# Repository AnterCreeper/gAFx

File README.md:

- core: main process board, including controller, FPGA, Audio DAC, EEPROM, battery charger and potentiometers(with buttons)
- pickguard: CAD file of pickguard
- pickup: Analog FrontEnd of pickup and Reflective Screen, sample signal from pickup and transport to main board via PDM signal in stereo
- plug: Plugs, including Type-C(may support Type-C Analog Headphone), SDcard, Headphone Out Jack, Line In Jack, Switch(mux between Bluetooth Receiver and Analog Line In)

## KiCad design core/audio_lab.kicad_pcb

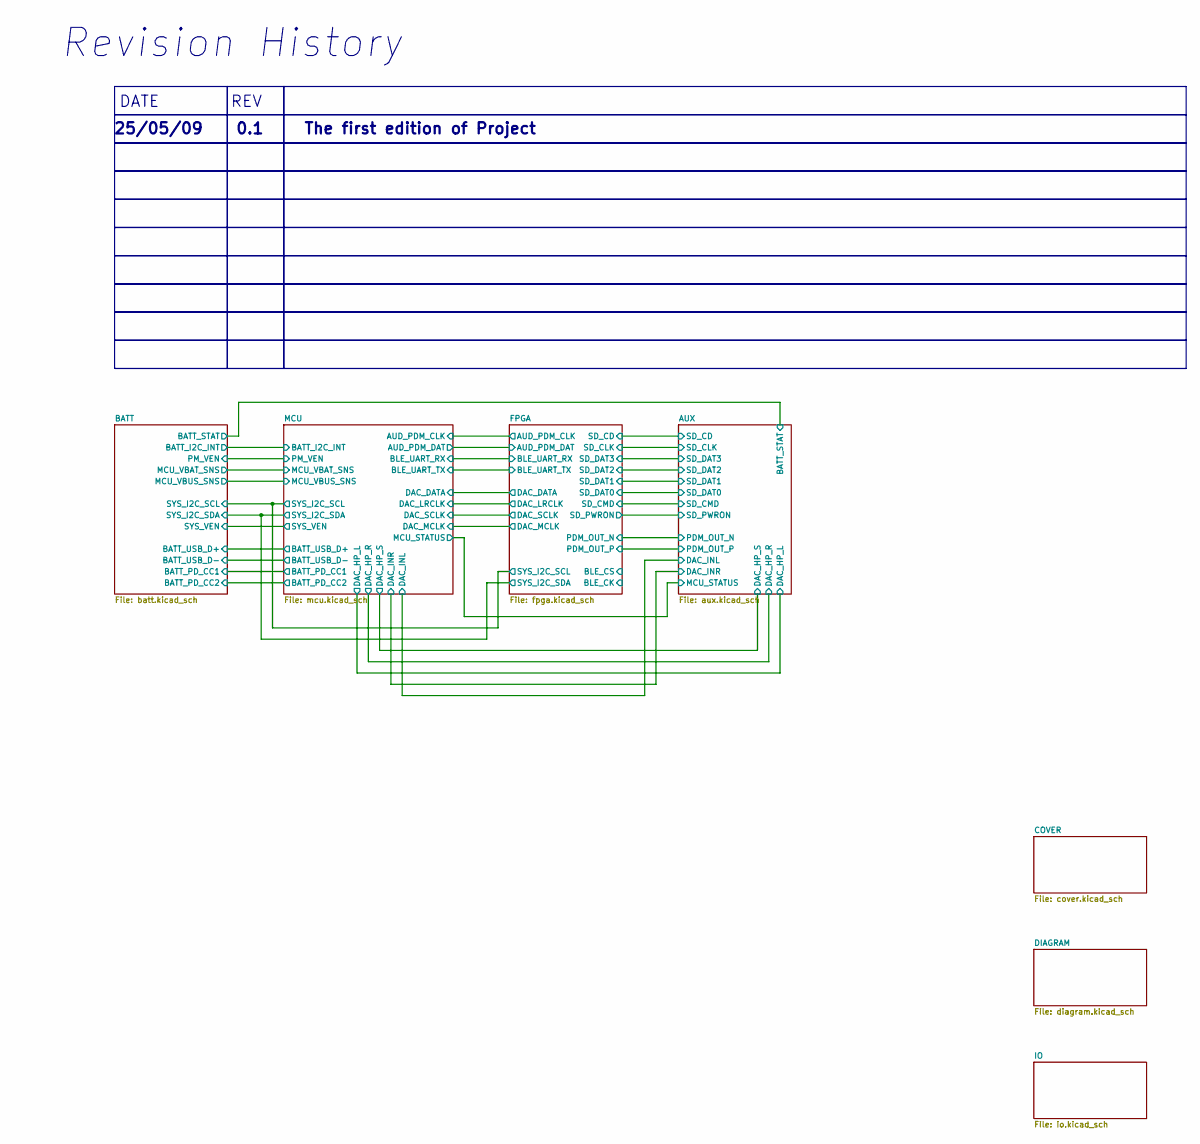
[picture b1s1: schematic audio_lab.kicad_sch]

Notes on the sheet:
Revision History
REV
0.1
25/05/09
The first edition of Project
DATE

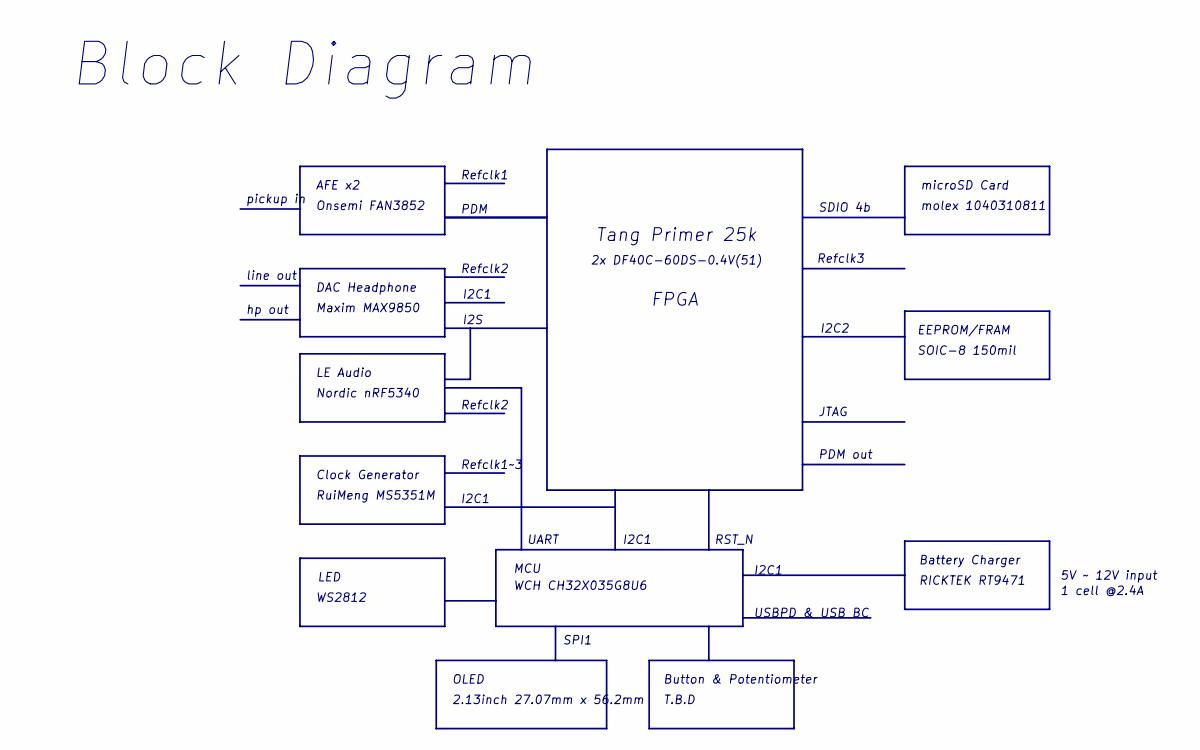
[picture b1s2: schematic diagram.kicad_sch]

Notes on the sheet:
T.B.D
Onsemi FAN3852
Clock Generator
line out
FPGA
PDM out
WCH CH32X035G8U6
5V ~ 12V input
Refclk2
RuiMeng MS5351M
USBPD & USB BC
Refclk3
JTAG
EEPROM/FRAM
Refclk1
I2C1
hp out
WS2812
microSD Card
SOIC-8 150mil
Maxim MAX9850
OLED
RICKTEK RT9471
molex 1040310811
Nordic nRF5340
LE Audio
PDM
Button & Potentiometer
Block Diagram
LED
pickup in
UART
DAC Headphone
I2C2
SDIO 4b
2.13inch 27.07mm x 56.2mm
AFE x2
SPI1
2x DF40C-60DS-0.4V(51)
MCU

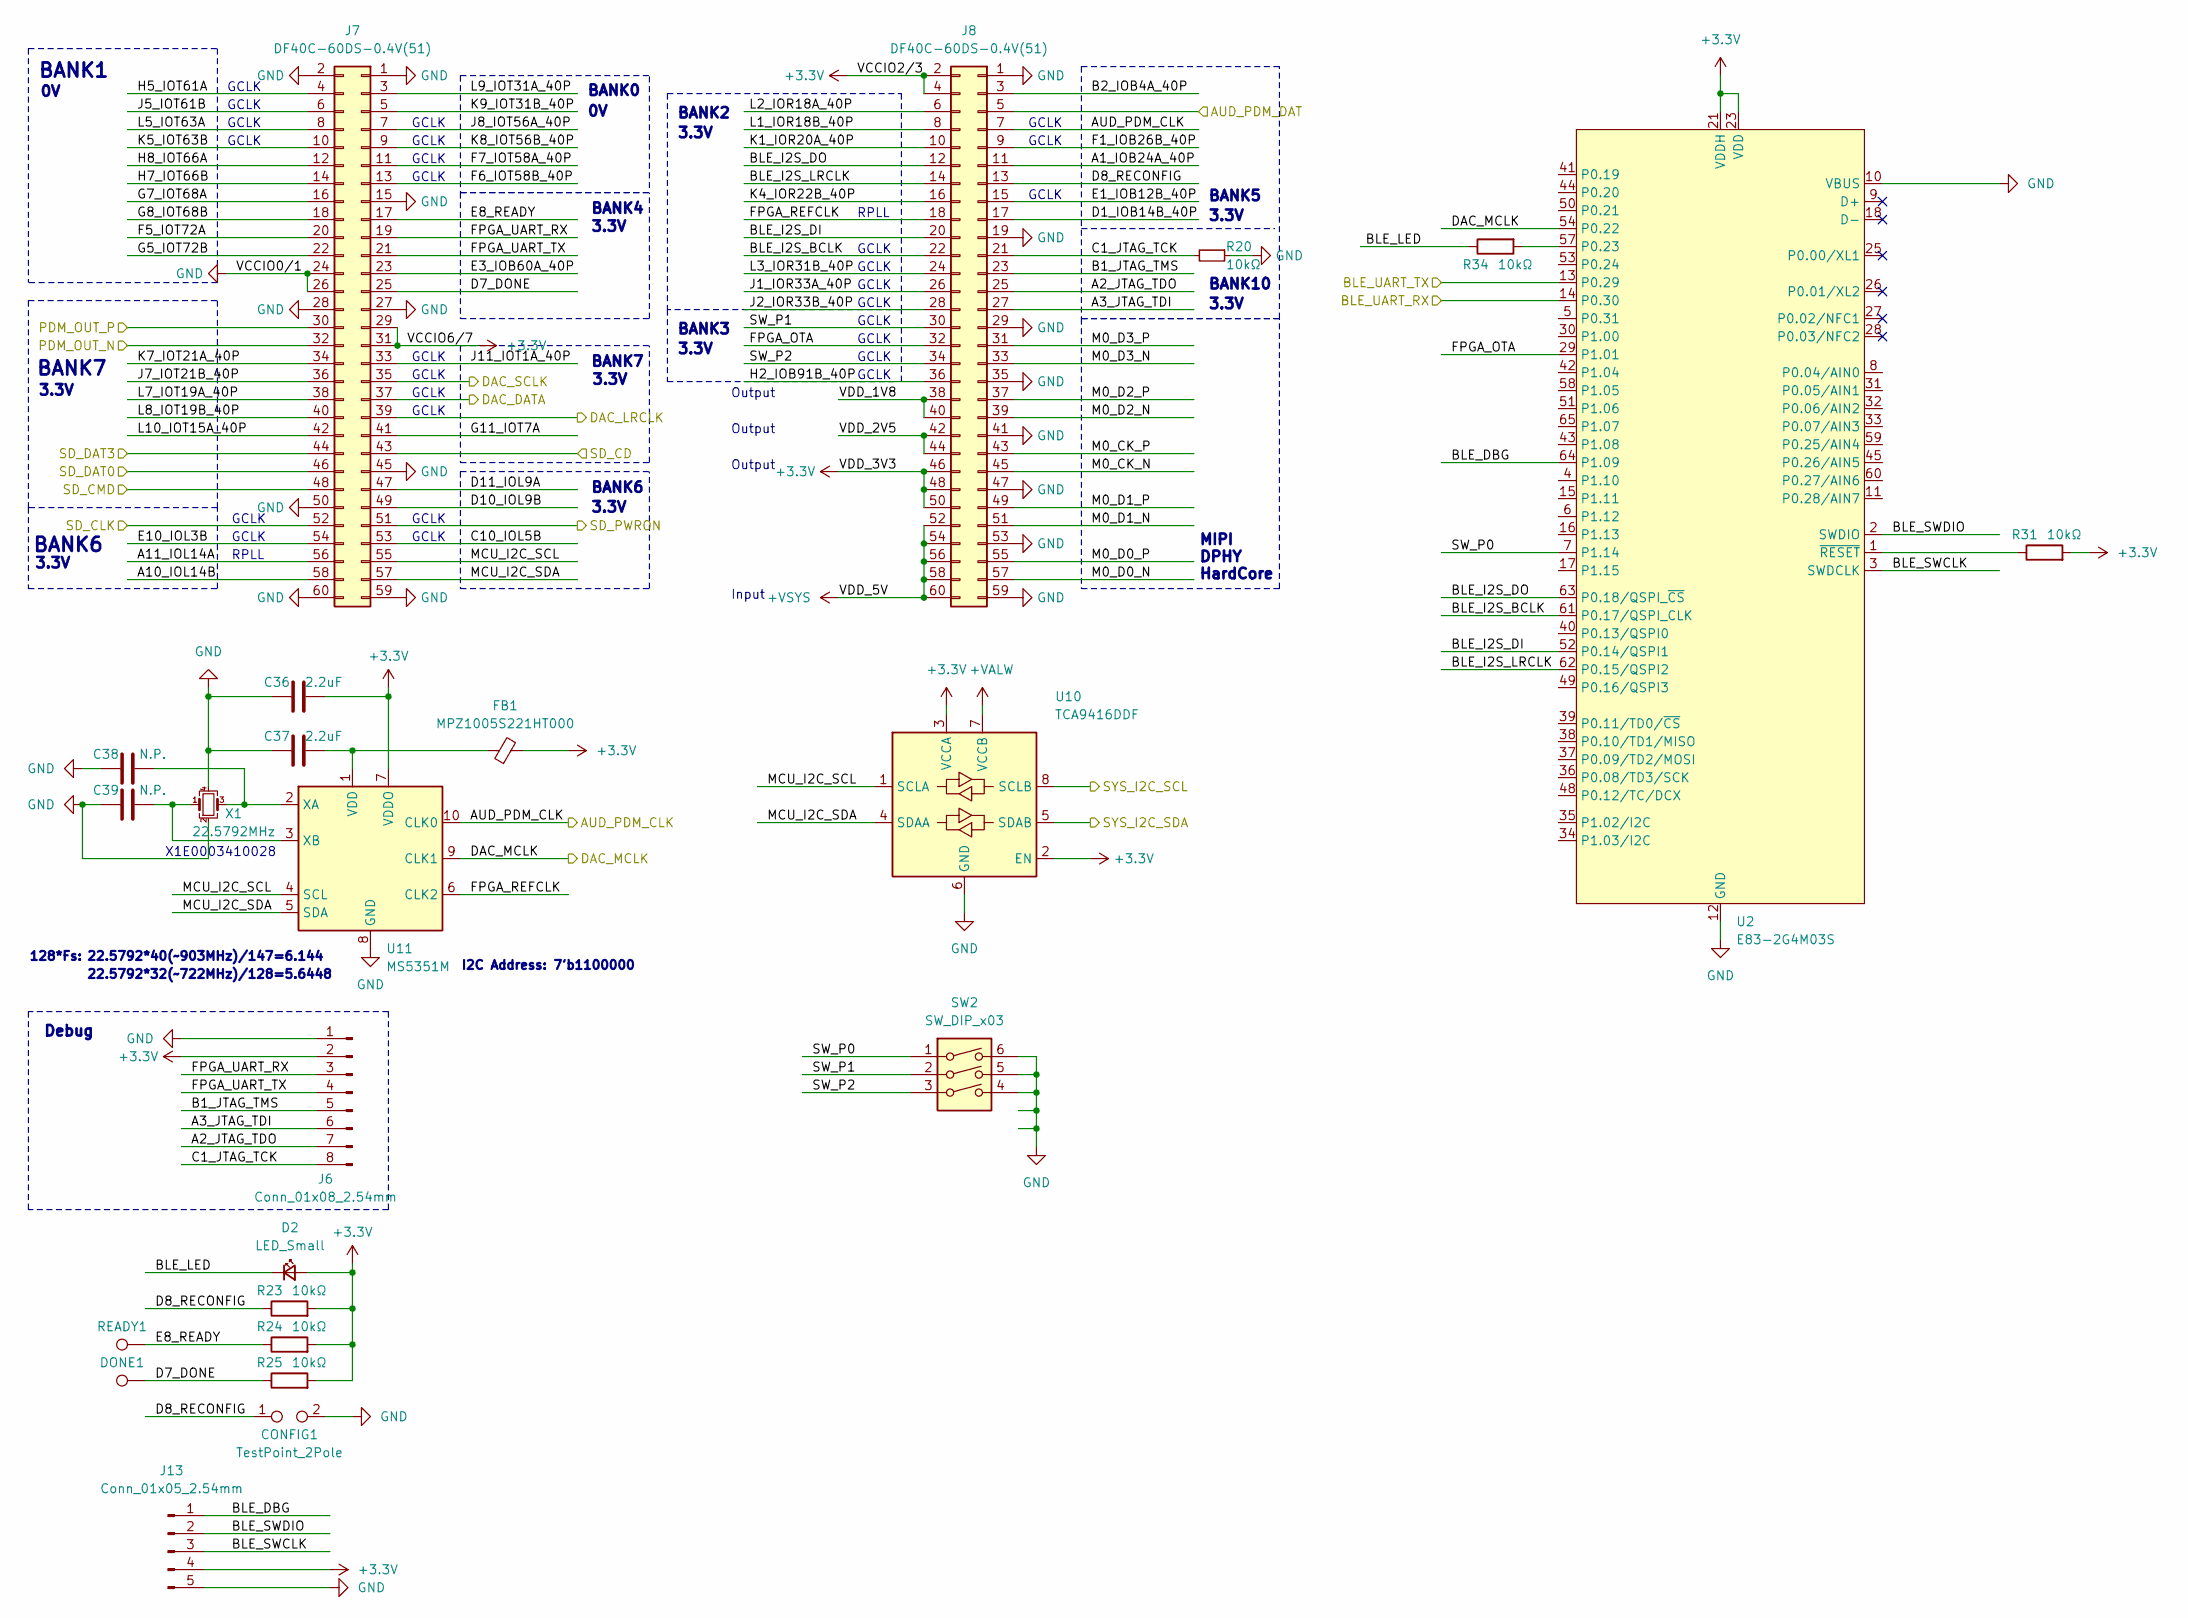
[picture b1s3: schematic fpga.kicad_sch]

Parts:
C36, C37: 2.2uF; C_0402_1005Metric
C38, C39: N.P.; C_0402_1005Metric
CONFIG1: TestPoint_2Pole; TestPoint_Bridge_Pitch2.0mm_Drill0.7mm
D2: LED_Small; D_0603_1608Metric
DONE1: TestPoint; TestPoint_Pad_D1.0mm
FB1: MPZ1005S221HT000; L_0402_1005Metric
J6: Conn_01x08_2.54mm; PinHeader_1x08_P2.54mm_Vertical
J7, J8: DF40C-60DS-0.4V(51); BTB-DF40C-60DS-0.4V(51)
J13: Conn_01x05_2.54mm; PinHeader_1x05_P2.54mm_Vertical
R20, R23, R24, R25, R31, R34: 10kΩ; R_0402_1005Metric
READY1: TestPoint; TestPoint_Pad_D1.0mm
SW2: SW_DIP_x03; SW_DIP_SPSTx03_Slide_KingTek_DSHP03TS_W7.62mm_P1.27mm
U2: E83-2G4M03S; E83-2G4M03S_16x16mm_LGA; LCSC C5333991
U10: TCA9416DDF; TSOT-23-8
U11: MS5351M; MSOP-10_3x3mm_P0.5mm
X1: 22.5792MHz; Crystal_SMD_3225-4Pin_3.2x2.5mm

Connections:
+3.3V: C36.2, D2.2 (A), FB1.2, J6.2, J7.29, J7.31, J8.2, J8.4, J8.46, J8.48, J8.50, J13.4, R23.2, R24.2, R25.2, R31.2, U2.21 (VDDH), U2.23 (VDD), U10.2 (EN), U10.3 (VCCA), U11.7 (VDDO); also elsewhere on the board
+VALW: U10.7 (VCCB); also elsewhere on the board
+VSYS: J8.52, J8.54, J8.56, J8.58, J8.60; also elsewhere on the board
/AUX/PDM_OUT_N: J7.32; also elsewhere on the board
/AUX/PDM_OUT_P: J7.30; also elsewhere on the board
/AUX/SD_CD: J7.43; also elsewhere on the board
/AUX/SD_CLK: J7.52; also elsewhere on the board
/AUX/SD_CMD: J7.48; also elsewhere on the board
/AUX/SD_DAT0: J7.46; also elsewhere on the board
/AUX/SD_DAT3: J7.44; also elsewhere on the board
/AUX/SD_PWRON: J7.51; also elsewhere on the board
/FPGA/A1_IOB24A_40P: J8.11
/FPGA/A2_JTAG_TDO: J6.7, J8.25
/FPGA/A3_JTAG_TDI: J6.6, J8.27
/FPGA/A10_IOL14B: J7.58
/FPGA/A11_IOL14A: J7.56
/FPGA/AUD_PDM_CLK: J8.7, U11.10 (CLK0); also elsewhere on the board
/FPGA/AUD_PDM_DAT: J8.5; also elsewhere on the board
/FPGA/B1_JTAG_TMS: J6.5, J8.23
/FPGA/B2_IOB4A_40P: J8.3
/FPGA/BLE_DBG: J13.1, U2.64 (P1.09)
/FPGA/BLE_I2S_BCLK: J8.22, U2.61 (P0.17/QSPI_CLK)
/FPGA/BLE_I2S_DI: J8.20, U2.52 (P0.14/QSPI1)
/FPGA/BLE_I2S_DO: J8.12, U2.63 (P0.18/QSPI_~CS)
/FPGA/BLE_I2S_LRCLK: J8.14, U2.62 (P0.15/QSPI2)
/FPGA/BLE_LED: D2.1 (K), R34.1
/FPGA/BLE_SWCLK: J13.3, U2.3 (SWDCLK)
/FPGA/BLE_SWDIO: J13.2, U2.2 (SWDIO)
/FPGA/BLE_UART_RX: U2.14 (P0.30); also elsewhere on the board
/FPGA/BLE_UART_TX: U2.13 (P0.29); also elsewhere on the board
/FPGA/C1_JTAG_TCK: J6.8, J8.21, R20.2
/FPGA/C10_IOL5B: J7.53
/FPGA/D1_IOB14B_40P: J8.17
/FPGA/D7_DONE: DONE1.1, J7.25, R25.1; also elsewhere on the board
/FPGA/D8_RECONFIG: CONFIG1.1, J8.13, R23.1; also elsewhere on the board
/FPGA/D10_IOL9B: J7.49
/FPGA/D11_IOL9A: J7.47
/FPGA/DAC_DATA: J7.37; also elsewhere on the board
/FPGA/DAC_LRCLK: J7.39; also elsewhere on the board
/FPGA/DAC_MCLK: U2.54 (P0.22), U11.9 (CLK1); also elsewhere on the board
/FPGA/DAC_SCLK: J7.35; also elsewhere on the board
/FPGA/E1_IOB12B_40P: J8.15
/FPGA/E3_IOB60A_40P: J7.23
/FPGA/E8_READY: J7.17, R24.1, READY1.1; also elsewhere on the board
/FPGA/E10_IOL3B: J7.54
/FPGA/F1_IOB26B_40P: J8.9
/FPGA/F5_IOT72A: J7.20
/FPGA/F6_IOT58B_40P: J7.13
/FPGA/F7_IOT58A_40P: J7.11
/FPGA/FPGA_OTA: J8.32, U2.29 (P1.01)
/FPGA/FPGA_REFCLK: J8.18, U11.6 (CLK2)
/FPGA/FPGA_UART_RX: J6.3, J7.19
/FPGA/FPGA_UART_TX: J6.4, J7.21
/FPGA/G5_IOT72B: J7.22
/FPGA/G7_IOT68A: J7.16
/FPGA/G8_IOT68B: J7.18
/FPGA/G11_IOT7A: J7.41
/FPGA/H2_IOB91B_40P: J8.36
/FPGA/H5_IOT61A: J7.4
/FPGA/H7_IOT66B: J7.14
/FPGA/H8_IOT66A: J7.12
/FPGA/J1_IOR33A_40P: J8.26
/FPGA/J2_IOR33B_40P: J8.28
/FPGA/J5_IOT61B: J7.6
/FPGA/J7_IOT21B_40P: J7.36
/FPGA/J8_IOT56A_40P: J7.7
/FPGA/J11_IOT1A_40P: J7.33
/FPGA/K1_IOR20A_40P: J8.10
/FPGA/K4_IOR22B_40P: J8.16
/FPGA/K5_IOT63B: J7.10
/FPGA/K7_IOT21A_40P: J7.34
/FPGA/K8_IOT56B_40P: J7.9
/FPGA/K9_IOT31B_40P: J7.5
/FPGA/L1_IOR18B_40P: J8.8
/FPGA/L2_IOR18A_40P: J8.6
/FPGA/L3_IOR31B_40P: J8.24
/FPGA/L5_IOT63A: J7.8
/FPGA/L7_IOT19A_40P: J7.38
/FPGA/L8_IOT19B_40P: J7.40
/FPGA/L9_IOT31A_40P: J7.3
/FPGA/L10_IOT15A_40P: J7.42
/FPGA/M0_CK_N: J8.45
/FPGA/M0_CK_P: J8.43
/FPGA/M0_D0_N: J8.57
/FPGA/M0_D0_P: J8.55
/FPGA/M0_D1_N: J8.51
/FPGA/M0_D1_P: J8.49
/FPGA/M0_D2_N: J8.39
/FPGA/M0_D2_P: J8.37
/FPGA/M0_D3_N: J8.33
/FPGA/M0_D3_P: J8.31
/FPGA/MCU_I2C_SCL: J7.55, U10.1 (SCLA), U11.4 (SCL)
/FPGA/MCU_I2C_SDA: J7.57, U10.4 (SDAA), U11.5 (SDA)
/FPGA/SW_P0: SW2.1, U2.7 (P1.14)
/FPGA/SW_P1: J8.30, SW2.2
/FPGA/SW_P2: J8.34, SW2.3
/FPGA/VDD_1V8: J8.38, J8.40
/FPGA/VDD_2V5: J8.42, J8.44
/MCU/MCU_I2C_SCL: U10.8 (SCLB); also elsewhere on the board
/MCU/MCU_I2C_SDA: U10.5 (SDAB); also elsewhere on the board
GND: C36.1, C37.1, C38.1, C39.1, CONFIG1.2, J6.1, J7.1, J7.2, J7.15, J7.24, J7.26, J7.27, J7.28, J7.45, J7.50, J7.59, J7.60, J8.1, J8.19, J8.29, J8.35, J8.41, J8.47, J8.53, J8.59, J13.5, R20.1, SW2.4, SW2.5, SW2.6, U2.10 (VBUS), U2.12 (GND), U2.19 (GND), U2.20 (GND), U2.22 (GND), U2.24 (GND), U2.46 (GND), U2.47 (GND), U2.55 (GND), U2.56 (GND), U10.6 (GND), U11.8 (GND), X1.2, X1.4; also elsewhere on the board
unnamed: R34.2, U2.57 (P0.23)
unnamed: R31.1, U2.1 (~RESET)
unnamed: C37.2, FB1.1, U11.1 (VDD)
unnamed: C38.2, U11.2 (XA), X1.3
unnamed: C39.2, U11.3 (XB), X1.1

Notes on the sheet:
GCLK
BANK6
RPLL
BANK2
22.5792*32(~722MHz)/128=5.6448
Debug
3.3V
BANK10
MIPI DPHY HardCore
BANK4
BANK5
X1E0003410028
Input
Output
BANK7
I2C Address: 7'b1100000
128*Fs:
BANK1
22.5792*40(~903MHz)/147=6.144
BANK3
BANK0

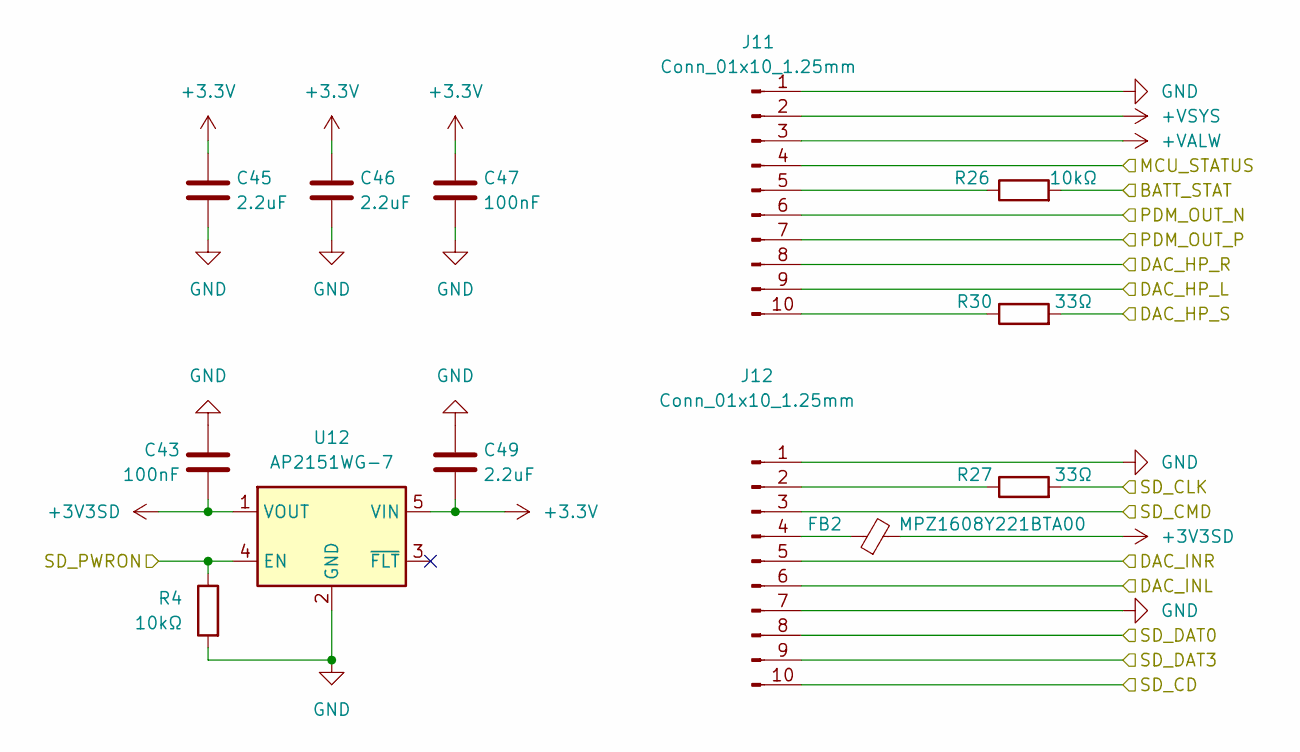
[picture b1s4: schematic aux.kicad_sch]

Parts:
C43, C47: 100nF; C_0402_1005Metric
C45, C46, C49: 2.2uF; C_0402_1005Metric
FB2: MPZ1608Y221BTA00; L_0603_1608Metric
J11, J12: Conn_01x10_1.25mm; Molex_PicoBlade_53047-1010_1x10_P1.25mm_Vertical
R4, R26: 10kΩ; R_0402_1005Metric
R27, R30: 33Ω; R_0402_1005Metric
U12: AP2151WG-7; SOT-23-5

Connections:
+3.3V: C45.1, C46.1, C47.1, C49.2, U12.5 (VIN); also elsewhere on the board
+3V3SD: C43.2, FB2.2, U12.1 (VOUT)
+VALW: J11.3; also elsewhere on the board
+VSYS: J11.2; also elsewhere on the board
/AUX/BATT_STAT: R26.2; also elsewhere on the board
/AUX/DAC_HP_L: J11.9; also elsewhere on the board
/AUX/DAC_HP_R: J11.8; also elsewhere on the board
/AUX/DAC_HP_S: R30.2; also elsewhere on the board
/AUX/DAC_INL: J12.6; also elsewhere on the board
/AUX/DAC_INR: J12.5; also elsewhere on the board
/AUX/MCU_STATUS: J11.4; also elsewhere on the board
/AUX/PDM_OUT_N: J11.6; also elsewhere on the board
/AUX/PDM_OUT_P: J11.7; also elsewhere on the board
/AUX/SD_CD: J12.10; also elsewhere on the board
/AUX/SD_CLK: R27.2; also elsewhere on the board
/AUX/SD_CMD: J12.3; also elsewhere on the board
/AUX/SD_DAT0: J12.8; also elsewhere on the board
/AUX/SD_DAT3: J12.9; also elsewhere on the board
/AUX/SD_PWRON: R4.1, U12.4 (EN); also elsewhere on the board
GND: C43.1, C45.2, C46.2, C47.2, C49.1, J11.1, J12.1, J12.7, R4.2, U12.2 (GND); also elsewhere on the board
unnamed: J11.5, R26.1
unnamed: J11.10, R30.1
unnamed: J12.2, R27.1
unnamed: FB2.1, J12.4

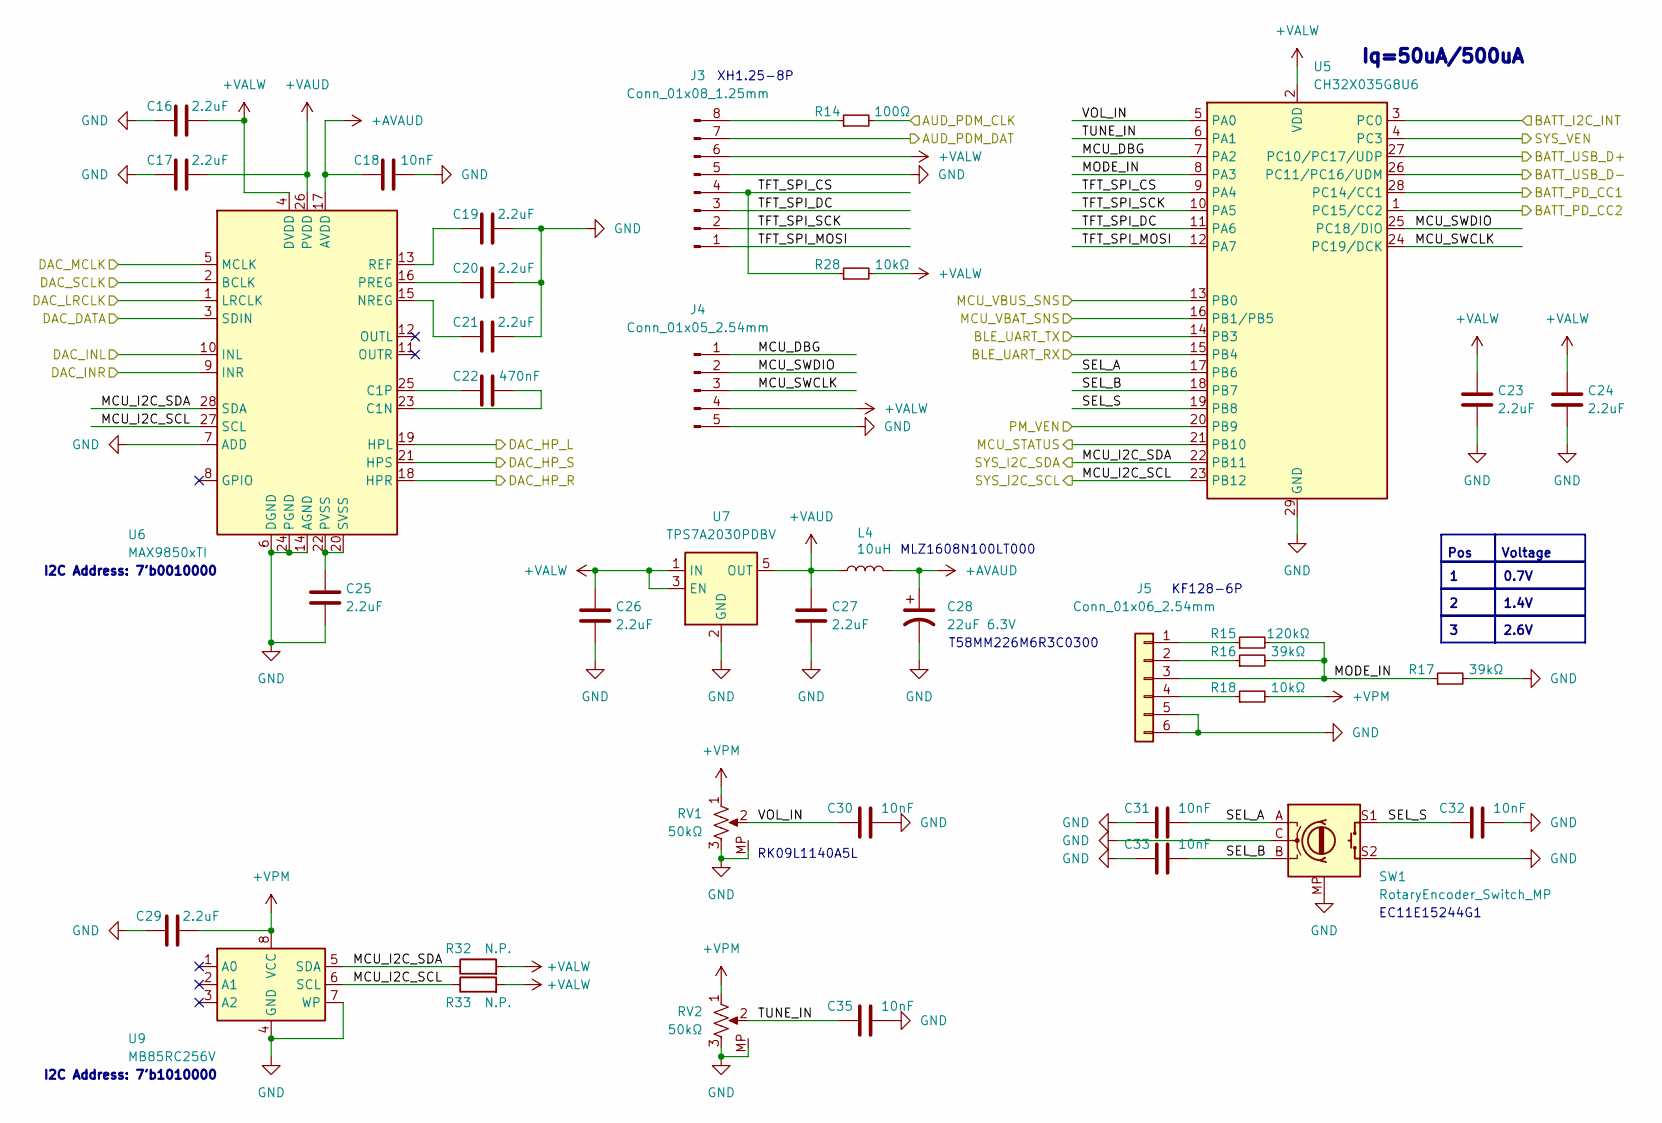
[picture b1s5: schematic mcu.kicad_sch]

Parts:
C16, C17, C19, C20, C21, C23, C24, C25, C26, C27, C29: 2.2uF; C_0402_1005Metric
C18, C30, C31, C32, C33, C35: 10nF; C_0402_1005Metric
C22: 470nF; C_0402_1005Metric
C28: 22uF 6.3V; CP_EIA-1608-08_AVX-J
J3: Conn_01x08_1.25mm; Molex_PicoBlade_53047-0810_1x08_P1.25mm_Vertical
J4: Conn_01x05_2.54mm; PinHeader_1x05_P2.54mm_Vertical
J5: Conn_01x06_2.54mm; PinSocket_1x06_P2.54mm_Vertical
L4: 10uH; L_0603_1608Metric
R14: 100Ω; R_0402_1005Metric
R15: 120kΩ; R_0402_1005Metric
R16, R17: 39kΩ; R_0402_1005Metric
R18, R28: 10kΩ; R_0402_1005Metric
R32, R33: N.P.; R_0402_1005Metric
RV1, RV2: 50kΩ; Potentiometer_Alpha_RD901F-40-00D_Single_Vertical
SW1: RotaryEncoder_Switch_MP; RotaryEncoder_Favor_FEC11_Vertical_H15mm
U5: CH32X035G8U6; QFN-28-1EP_4x4mm_P0.4mm_EP2.7x2.7mm
U6: MAX9850xTI; TQFN-28-1EP_5x5mm_P0.5mm_EP3.25x3.25mm_ThermalVias
U7: TPS7A2030PDBV; SOT-23-5
U9: MB85RC256V; SOIC-8_3.9x4.9mm_P1.27mm

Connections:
+AVAUD: C18.1, C28.1, L4.2, U6.17 (AVDD)
+VALW: C16.2, C23.1, C24.1, C26.1, J3.6, J4.4, R28.2, R32.2, R33.2, U5.2 (VDD), U6.4 (DVDD), U7.1 (IN), U7.3 (EN); also elsewhere on the board
+VAUD: C17.2, C27.1, L4.1, U6.26 (PVDD), U7.5 (OUT)
+VPM: C29.2, R18.2, RV1.1, RV2.1, U9.8 (VCC); also elsewhere on the board
/AUX/DAC_HP_L: U6.19 (HPL); also elsewhere on the board
/AUX/DAC_HP_R: U6.18 (HPR); also elsewhere on the board
/AUX/DAC_HP_S: U6.21 (HPS); also elsewhere on the board
/AUX/DAC_INL: U6.10 (INL); also elsewhere on the board
/AUX/DAC_INR: U6.9 (INR); also elsewhere on the board
/AUX/MCU_STATUS: U5.21 (PB10); also elsewhere on the board
/BATT/BATT_I2C_INT: U5.3 (PC0); also elsewhere on the board
/BATT/BATT_PD_CC1: U5.28 (PC14/CC1); also elsewhere on the board
/BATT/BATT_PD_CC2: U5.1 (PC15/CC2); also elsewhere on the board
/BATT/BATT_USB_D+: U5.27 (PC10/PC17/UDP); also elsewhere on the board
/BATT/BATT_USB_D-: U5.26 (PC11/PC16/UDM); also elsewhere on the board
/BATT/MCU_VBAT_SNS: U5.16 (PB1/PB5); also elsewhere on the board
/BATT/MCU_VBUS_SNS: U5.13 (PB0); also elsewhere on the board
/BATT/PM_VEN: U5.20 (PB9); also elsewhere on the board
/BATT/SYS_VEN: U5.4 (PC3); also elsewhere on the board
/FPGA/AUD_PDM_CLK: R14.2; also elsewhere on the board
/FPGA/AUD_PDM_DAT: J3.7; also elsewhere on the board
/FPGA/BLE_UART_RX: U5.15 (PB4); also elsewhere on the board
/FPGA/BLE_UART_TX: U5.14 (PB3); also elsewhere on the board
/FPGA/DAC_DATA: U6.3 (SDIN); also elsewhere on the board
/FPGA/DAC_LRCLK: U6.1 (LRCLK); also elsewhere on the board
/FPGA/DAC_MCLK: U6.5 (MCLK); also elsewhere on the board
/FPGA/DAC_SCLK: U6.2 (BCLK); also elsewhere on the board
/MCU/MCU_DBG: J4.1, U5.7 (PA2)
/MCU/MCU_I2C_SCL: R33.1, U5.23 (PB12), U6.27 (SCL), U9.6 (SCL); also elsewhere on the board
/MCU/MCU_I2C_SDA: R32.1, U5.22 (PB11), U6.28 (SDA), U9.5 (SDA); also elsewhere on the board
/MCU/MCU_SWCLK: J4.3, U5.24 (PC19/DCK)
/MCU/MCU_SWDIO: J4.2, U5.25 (PC18/DIO)
/MCU/MODE_IN: J5.3, R15.2, R16.2, R17.1, U5.8 (PA3)
/MCU/SEL_A: C31.2, SW1.A, U5.17 (PB6)
/MCU/SEL_B: C33.2, SW1.B, U5.18 (PB7)
/MCU/SEL_S: C32.1, SW1.S1, U5.19 (PB8)
/MCU/TFT_SPI_CS: J3.4, R28.1, U5.9 (PA4)
/MCU/TFT_SPI_DC: J3.3, U5.11 (PA6)
/MCU/TFT_SPI_MOSI: J3.1, U5.12 (PA7)
/MCU/TFT_SPI_SCK: J3.2, U5.10 (PA5)
/MCU/TUNE_IN: C35.1, RV2.2, U5.6 (PA1)
/MCU/VOL_IN: C30.1, RV1.2, U5.5 (PA0)
GND: C16.1, C17.1, C18.2, C19.2, C20.2, C21.2, C23.2, C24.2, C25.2, C26.2, C27.2, C28.2, C29.1, C30.2, C31.1, C32.2, C33.1, C35.2, J3.5, J4.5, J5.5, J5.6, R17.2, RV1.3, RV1.MP, RV2.3, RV2.MP, SW1.C, SW1.MP, SW1.S2, U5.29 (GND), U6.6 (DGND), U6.7 (ADD), U6.14 (AGND), U6.24 (PGND), U6.29 (AGND), U7.2 (GND), U9.4 (GND), U9.7 (WP); also elsewhere on the board
unnamed: J3.8, R14.1
unnamed: J5.1, R15.1
unnamed: J5.2, R16.1
unnamed: J5.4, R18.1
unnamed: C22.2, U6.23 (C1N)
unnamed: C22.1, U6.25 (C1P)
unnamed: C21.1, U6.15 (NREG)
unnamed: C20.1, U6.16 (PREG)
unnamed: C25.1, U6.20 (SVSS), U6.22 (PVSS)
unnamed: C19.1, U6.13 (REF)

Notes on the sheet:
T58MM226M6R3C0300
Pos
Iq=50uA/500uA
RK09L1140A5L
MLZ1608N100LT000
0.7V
1.4V
XH1.25-8P
2.6V
I2C Address: 7'b1010000
Voltage
I2C Address: 7'b0010000
KF128-6P
EC11E15244G1

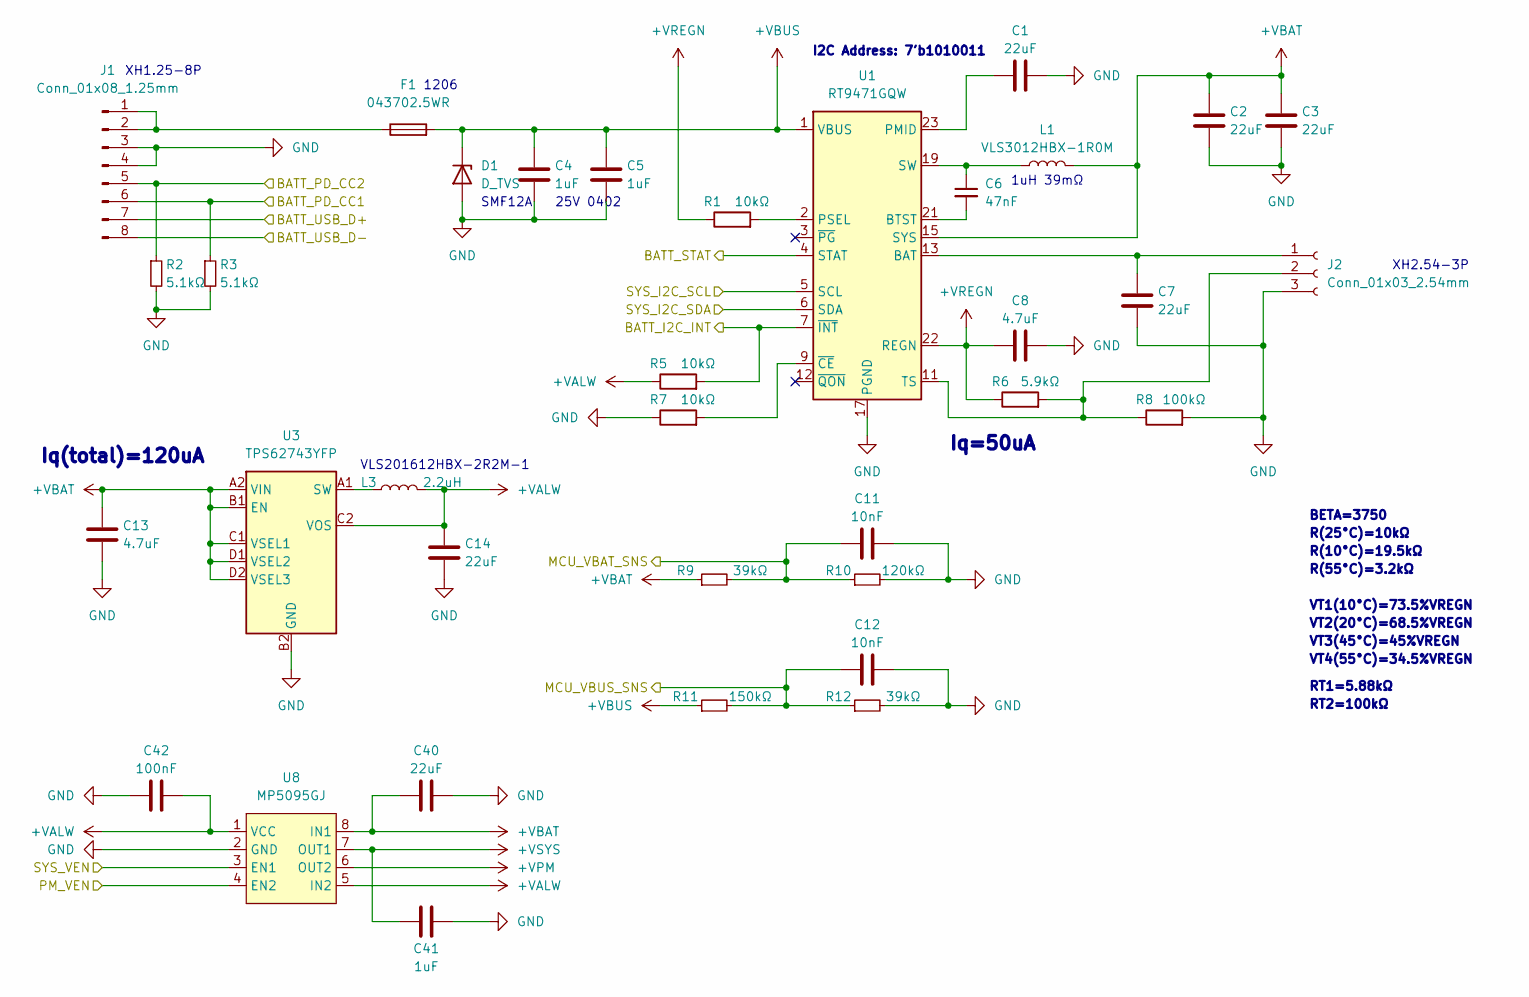
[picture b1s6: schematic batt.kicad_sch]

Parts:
C1, C2, C3, C7, C14, C40: 22uF; C_0603_1608Metric
C4, C5, C41: 1uF; C_0402_1005Metric
C6: 47nF; C_0402_1005Metric
C8, C13: 4.7uF; C_0402_1005Metric
C11, C12: 10nF; C_0402_1005Metric
C42: 100nF; C_0402_1005Metric
D1: D_TVS; D_PowerDI-123
F1: 043702.5WR; Fuse_1206_3216Metric
J1: Conn_01x08_1.25mm; Molex_PicoBlade_53047-0810_1x08_P1.25mm_Vertical
J2: Conn_01x03_2.54mm; JST_XH_B3B-XH-A_1x03_P2.50mm_Vertical
L1: VLS3012HBX-1R0M; L_TDK_VLS3012HBX
L3: 2.2uH; L_Murata_DFE201610P
R1, R5, R7: 10kΩ; R_0402_1005Metric
R2, R3: 5.1kΩ; R_0402_1005Metric
R6: 5.9kΩ; R_0402_1005Metric
R8: 100kΩ; R_0402_1005Metric
R9, R12: 39kΩ; R_0402_1005Metric
R10: 120kΩ; R_0402_1005Metric
R11: 150kΩ; R_0402_1005Metric
U1: RT9471GQW; RICKTEK_WQFN-24-1EP_4x4mm_P0.5mm_EP2.6x2.6mm_ThermalVias
U3: TPS62743YFP; Texas_DSBGA-8_0.86x1.56mm_Layout2x4_P0.4mm
U8: MP5095GJ; TSOT-23-8

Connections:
+VALW: C14.1, C42.2, L3.2, R5.1, U3.C2 (VOS), U8.1 (VCC), U8.5 (IN2); also elsewhere on the board
+VBAT: C2.1, C3.1, C13.1, C40.1, L1.2, R9.1, U1.15 (SYS), U1.16 (SYS), U3.A2 (VIN), U3.B1 (EN), U3.C1 (VSEL1), U3.D1 (VSEL2), U3.D2 (VSEL3), U8.8 (IN1)
+VBUS: C4.1, C5.1, D1.1 (K), F1.2, R11.1, U1.1 (VBUS), U1.24 (VBUS)
+VPM: U8.6 (OUT2); also elsewhere on the board
+VREGN: C8.1, R1.1, R6.1, U1.22 (REGN)
+VSYS: C41.1, U8.7 (OUT1); also elsewhere on the board
/AUX/BATT_STAT: U1.4 (STAT); also elsewhere on the board
/BATT/BATT_I2C_INT: R5.2, U1.7 (~INT); also elsewhere on the board
/BATT/BATT_PD_CC1: J1.6, R3.1; also elsewhere on the board
/BATT/BATT_PD_CC2: J1.5, R2.1; also elsewhere on the board
/BATT/BATT_USB_D+: J1.7; also elsewhere on the board
/BATT/BATT_USB_D-: J1.8; also elsewhere on the board
/BATT/MCU_VBAT_SNS: C11.1, R9.2, R10.1; also elsewhere on the board
/BATT/MCU_VBUS_SNS: C12.1, R11.2, R12.1; also elsewhere on the board
/BATT/PM_VEN: U8.4 (EN2); also elsewhere on the board
/BATT/SYS_VEN: U8.3 (EN1); also elsewhere on the board
/MCU/MCU_I2C_SCL: U1.5 (SCL); also elsewhere on the board
/MCU/MCU_I2C_SDA: U1.6 (SDA); also elsewhere on the board
GND: C1.2, C2.2, C3.2, C4.2, C5.2, C7.2, C8.2, C11.2, C12.2, C13.2, C14.2, C40.2, C41.2, C42.1, D1.2 (A), J1.3, J1.4, J2.3, R2.2, R3.2, R7.1, R8.2, R10.2, R12.2, U1.17 (PGND), U1.18 (PGND), U1.25 (PGND), U3.B2 (GND), U8.2 (GND); also elsewhere on the board
unnamed: C6.1, L1.1, U1.19 (SW), U1.20 (SW)
unnamed: F1.1, J1.1, J1.2
unnamed: C7.1, J2.1, U1.13 (BAT), U1.14 (BAT)
unnamed: J2.2, R6.2, R8.1, U1.11 (TS)
unnamed: C6.2, U1.21 (BTST)
unnamed: C1.1, U1.23 (PMID)
unnamed: R1.2, U1.2 (PSEL)
unnamed: R7.2, U1.9 (~CE)
unnamed: L3.1, U3.A1 (SW)

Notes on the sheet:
1uH 39mΩ
RT2=100kΩ
VT2(20°C)=68.5%VREGN
Iq(total)=120uA
XH2.54-3P
BETA=3750
VLS201612HBX-2R2M-1
VT4(55°C)=34.5%VREGN
Iq=50uA
25V 0402
VT1(10°C)=73.5%VREGN
XH1.25-8P
RT1=5.88kΩ
VT3(45°C)=45%VREGN
R(10°C)=19.5kΩ
1206
R(55°C)=3.2kΩ
R(25°C)=10kΩ
I2C Address: 7'b1010011
SMF12A

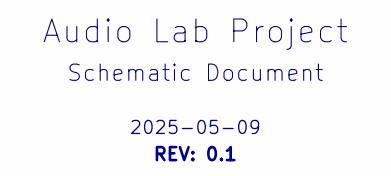
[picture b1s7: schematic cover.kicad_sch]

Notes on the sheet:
2025-05-09
Schematic Document
REV: 0.1
Audio Lab Project

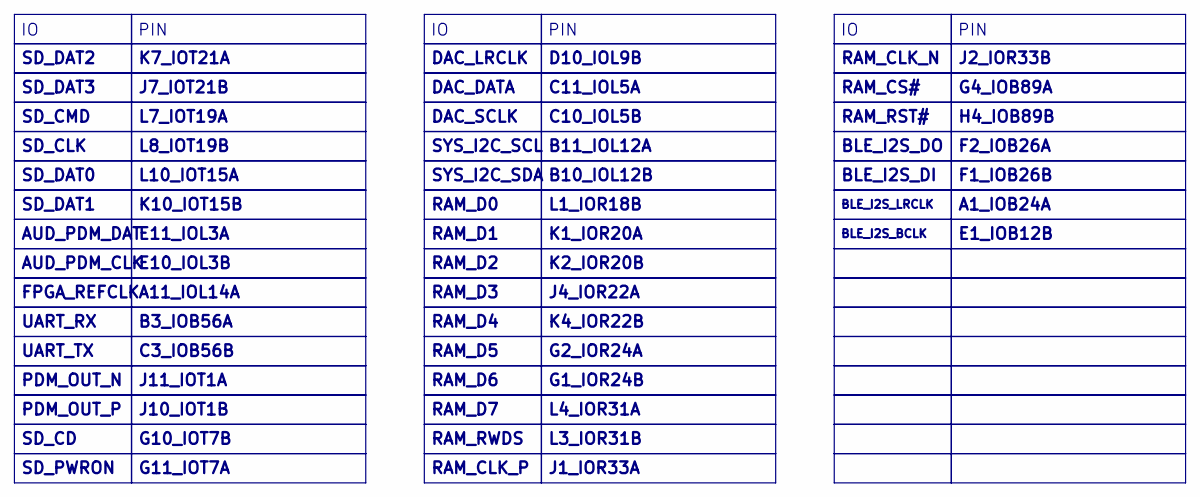
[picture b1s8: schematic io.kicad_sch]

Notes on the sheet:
E10_IOL3B
E1_IOB12B
BLE_I2S_LRCLK
UART_RX
G10_IOT7B
RAM_RWDS
RAM_RST#
C3_IOB56B
C10_IOL5B
F2_IOB26A
K7_IOT21A
A1_IOB24A
SYS_I2C_SCL
RAM_CLK_P
G11_IOT7A
AUD_PDM_DAT
SD_PWRON
RAM_CS#
G4_IOB89A
J10_IOT1B
K10_IOT15B
UART_TX
K1_IOR20A
K4_IOR22B
DAC_DATA
B10_IOL12B
SD_CLK
G1_IOR24B
H4_IOB89B
RAM_D5
G2_IOR24A
L1_IOR18B
L8_IOT19B
F1_IOB26B
RAM_D1
BLE_I2S_DO
PIN
SD_DAT1
AUD_PDM_CLK
SD_CMD

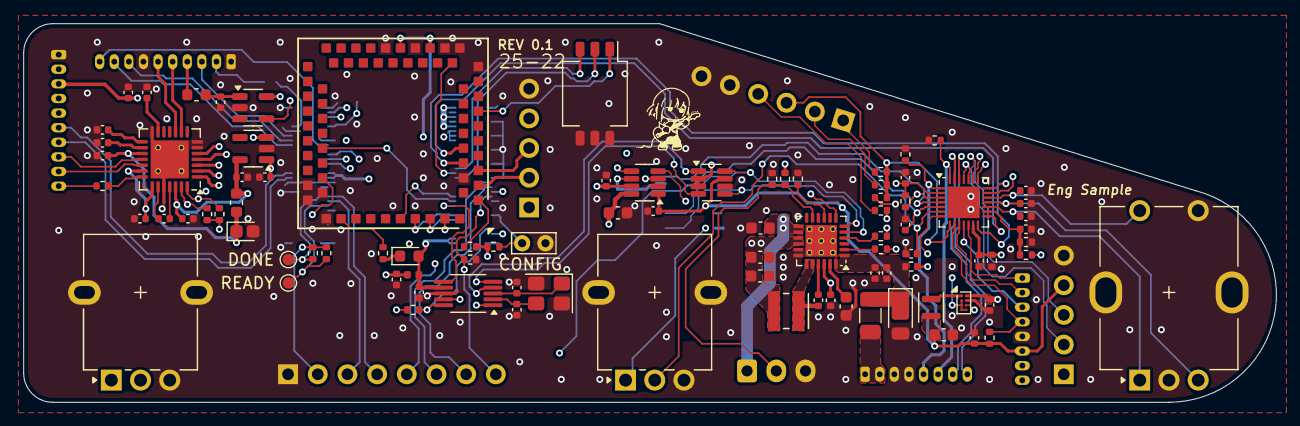
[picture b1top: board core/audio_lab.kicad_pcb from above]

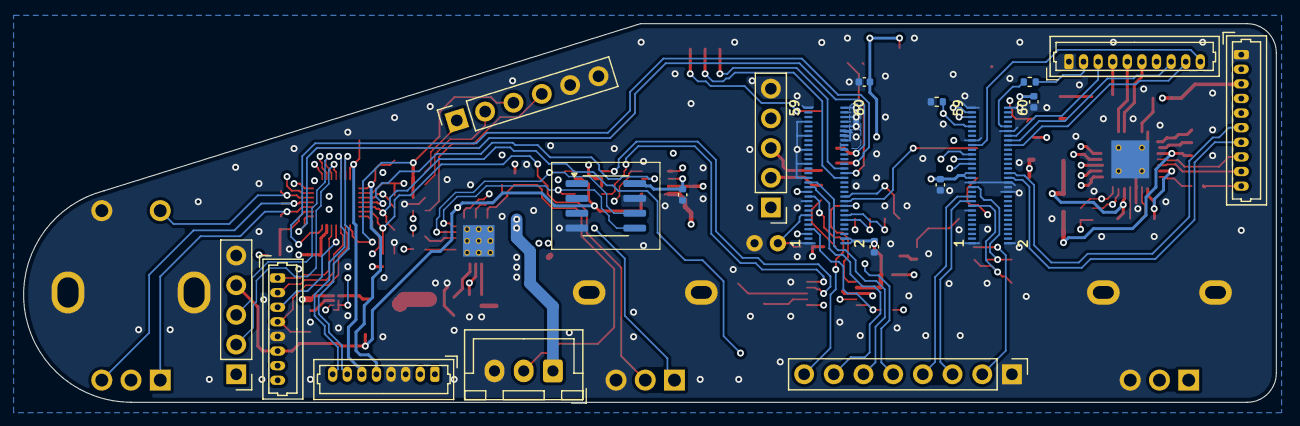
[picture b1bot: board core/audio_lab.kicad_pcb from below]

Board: 4 copper layers, 107.2 x 32.4 mm, 110 parts (19 on the bottom side), 112 nets.

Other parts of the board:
CONFIG: TestPoint_2Pole; TestPoint_Bridge_Pitch2.0mm_Drill0.7mm
DONE: TestPoint; TestPoint_Pad_D1.0mm
READY: TestPoint; TestPoint_Pad_D1.0mm

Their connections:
/FPGA/D7_DONE: DONE.1; also elsewhere on the board
/FPGA/D8_RECONFIG: CONFIG.1; also elsewhere on the board
/FPGA/E8_READY: READY.1; also elsewhere on the board
GND: CONFIG.2; also elsewhere on the board

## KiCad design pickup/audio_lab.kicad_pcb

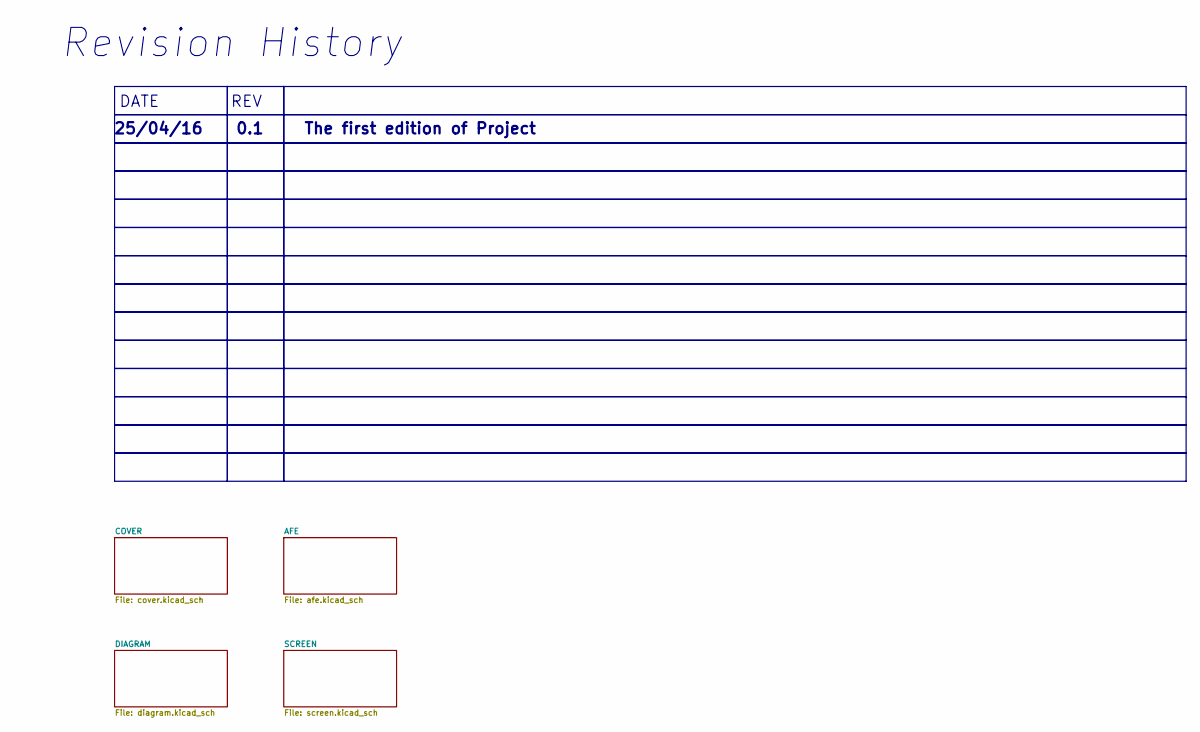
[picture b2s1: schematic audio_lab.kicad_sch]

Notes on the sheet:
Revision History
REV
0.1
25/04/16
The first edition of Project
DATE
